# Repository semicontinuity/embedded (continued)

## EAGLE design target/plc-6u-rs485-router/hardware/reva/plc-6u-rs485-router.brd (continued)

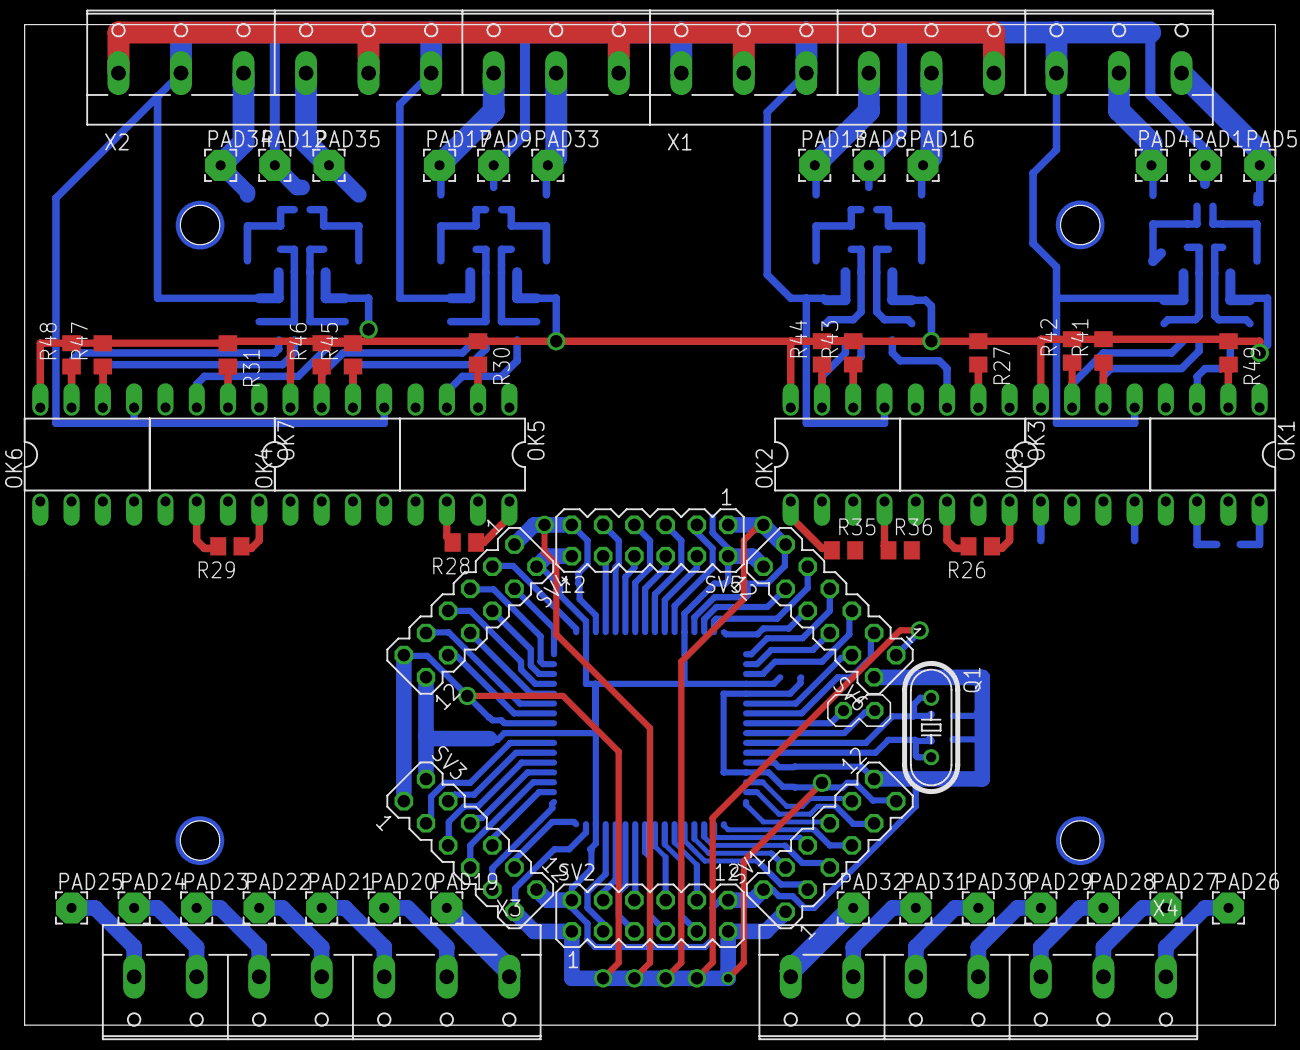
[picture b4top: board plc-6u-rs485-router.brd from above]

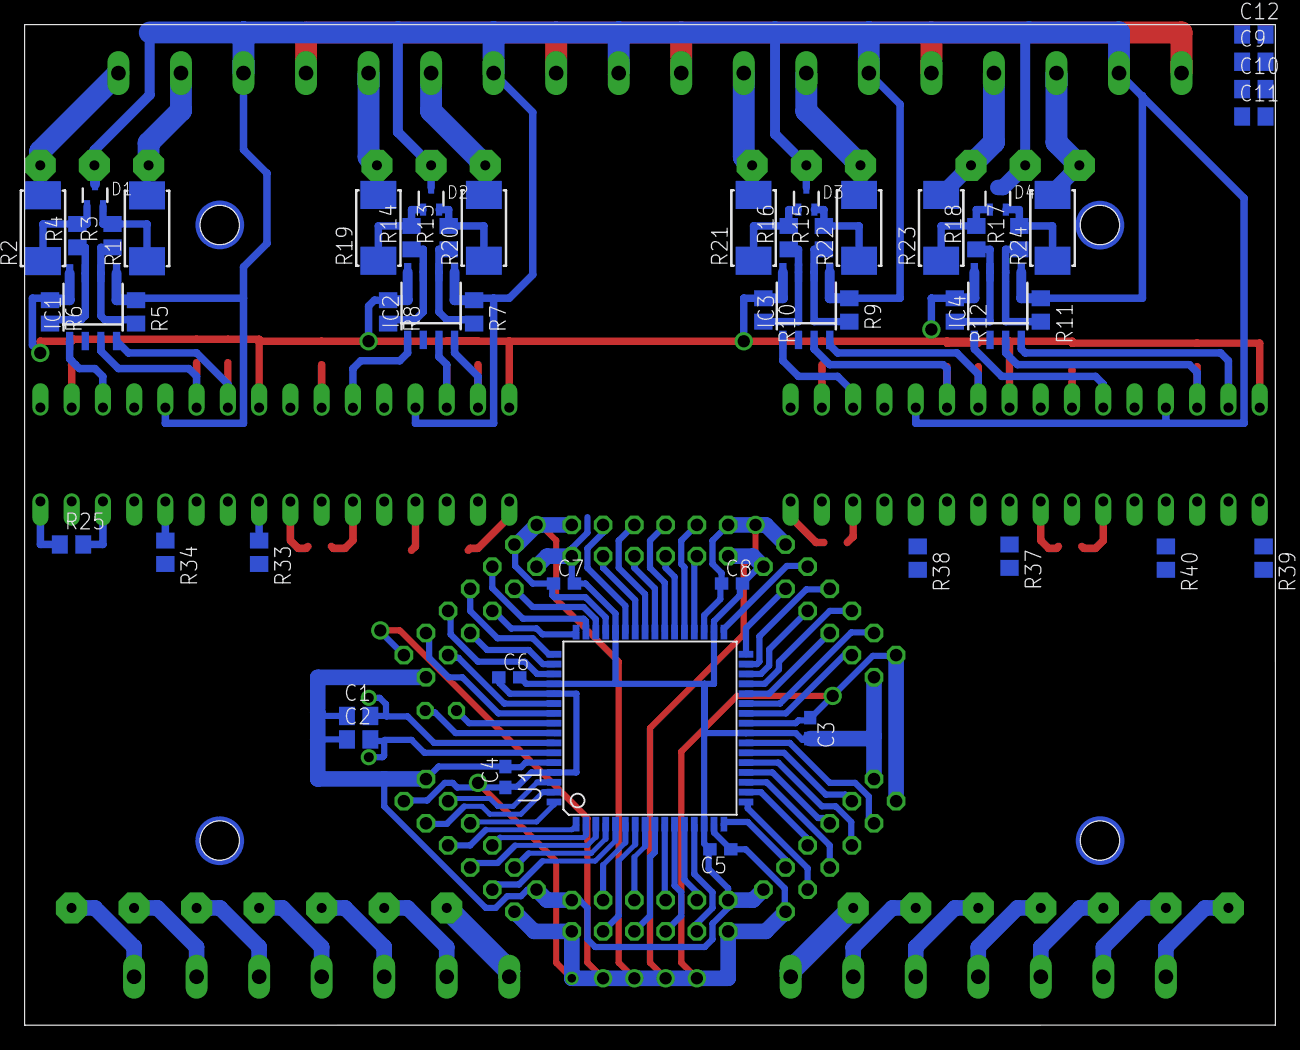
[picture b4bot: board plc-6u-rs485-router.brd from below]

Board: 2 copper layers, 101.6 x 81.3 mm, 115 parts (52 on the bottom side), 123 nets.

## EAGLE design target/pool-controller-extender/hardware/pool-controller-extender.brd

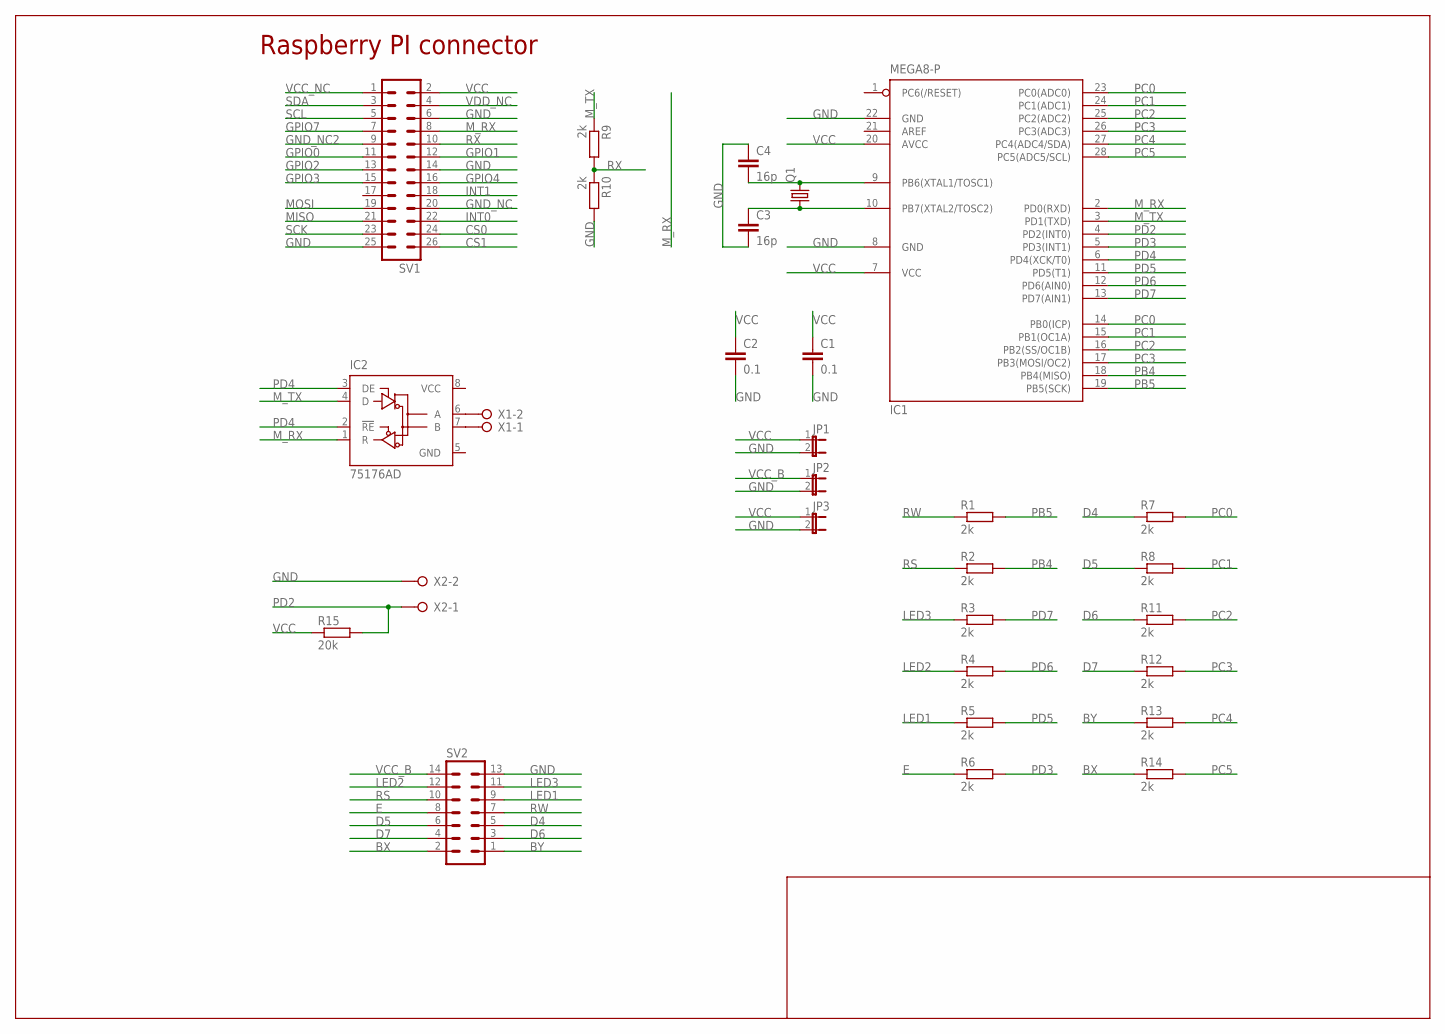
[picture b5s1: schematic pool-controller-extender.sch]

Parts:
C1, C2: 0.1; C0805
C3, C4: 16p; C0805
IC1: MEGA8-P; DIL28-3
IC2: 75176AD; D_R-PDSO-G8
JP1, JP2, JP3: JP1E; JP1
Q1: CRYSTALHC49S; HC49/S
R1, R2, R3, R4, R5, R6, R7, R8, R9, R10, R11, R12, R13, R14: 2k; R0805
R15: 20k; R0805
SV1: MA13-2
SV2: MA07-2W
X1, X2: W237-02P; W237-132

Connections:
BX: R14.1, SV2.2
BY: R13.1, SV2.1
CS0: SV1.24
CS1: SV1.26
D4: R7.1, SV2.5
D5: R8.1, SV2.6
D6: R11.1, SV2.3
D7: R12.1, SV2.4
E: R6.1, SV2.8
GND: C1.2, C2.2, C3.2, C4.1, IC1.8 (GND), IC1.22 (GND), IC2.5 (GND), JP1.2, JP2.2, JP3.2, R10.2, SV1.6, SV1.14, SV1.25, SV2.13, X2.2
GND_NC: SV1.20
GND_NC2: SV1.9
GPIO0: SV1.11
GPIO1: SV1.12
GPIO2: SV1.13
GPIO3: SV1.15
GPIO4: SV1.16
GPIO7: SV1.7
INT0: SV1.22
INT1: SV1.18
LED1: R5.1, SV2.9
LED2: R4.1, SV2.12
LED3: R3.1, SV2.11
MISO: SV1.21
MOSI: SV1.19
M_RX: IC1.2 (PD0(RXD)), IC2.1 (R), SV1.8
M_TX: IC1.3 (PD1(TXD)), IC2.4 (D), R9.1
unnamed: IC2.6 (A), X1.2
unnamed: IC2.7 (B), X1.1
unnamed: C3.1, IC1.10 (PB7(XTAL2/TOSC2)), Q1.1
unnamed: C4.2, IC1.9 (PB6(XTAL1/TOSC1)), Q1.2
PB4: IC1.18 (PB4(MISO)), R2.2
PB5: IC1.19 (PB5(SCK)), R1.2
PC0: IC1.14 (PB0(ICP)), IC1.23 (PC0(ADC0)), R7.2
PC1: IC1.15 (PB1(OC1A)), IC1.24 (PC1(ADC1)), R8.2
PC2: IC1.16 (PB2(SS/OC1B)), IC1.25 (PC2(ADC2)), R11.2
PC3: IC1.17 (PB3(MOSI/OC2)), IC1.26 (PC3(ADC3)), R12.2
PC4: IC1.27 (PC4(ADC4/SDA)), R13.2
PC5: IC1.28 (PC5(ADC5/SCL)), R14.2
PD2: IC1.4 (PD2(INT0)), R15.2, X2.1
PD3: IC1.5 (PD3(INT1)), R6.2
PD4: IC1.6 (PD4(XCK/T0)), IC2.2 (!RE), IC2.3 (DE)
PD5: IC1.11 (PD5(T1)), R5.2
PD6: IC1.12 (PD6(AIN0)), R4.2
PD7: IC1.13 (PD7(AIN1)), R3.2
RS: R2.1, SV2.10
RW: R1.1, SV2.7
RX: R9.2, R10.1, SV1.10
SCK: SV1.23
SCL: SV1.5
SDA: SV1.3
VCC: C1.1, C2.1, IC1.7 (VCC), IC1.20 (AVCC), IC2.8 (VCC), JP1.1, JP3.1, R15.1, SV1.2
VCC_B: JP2.1, SV2.14
VCC_NC: SV1.1
VDD_NC: SV1.4

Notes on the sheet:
Raspberry PI connector

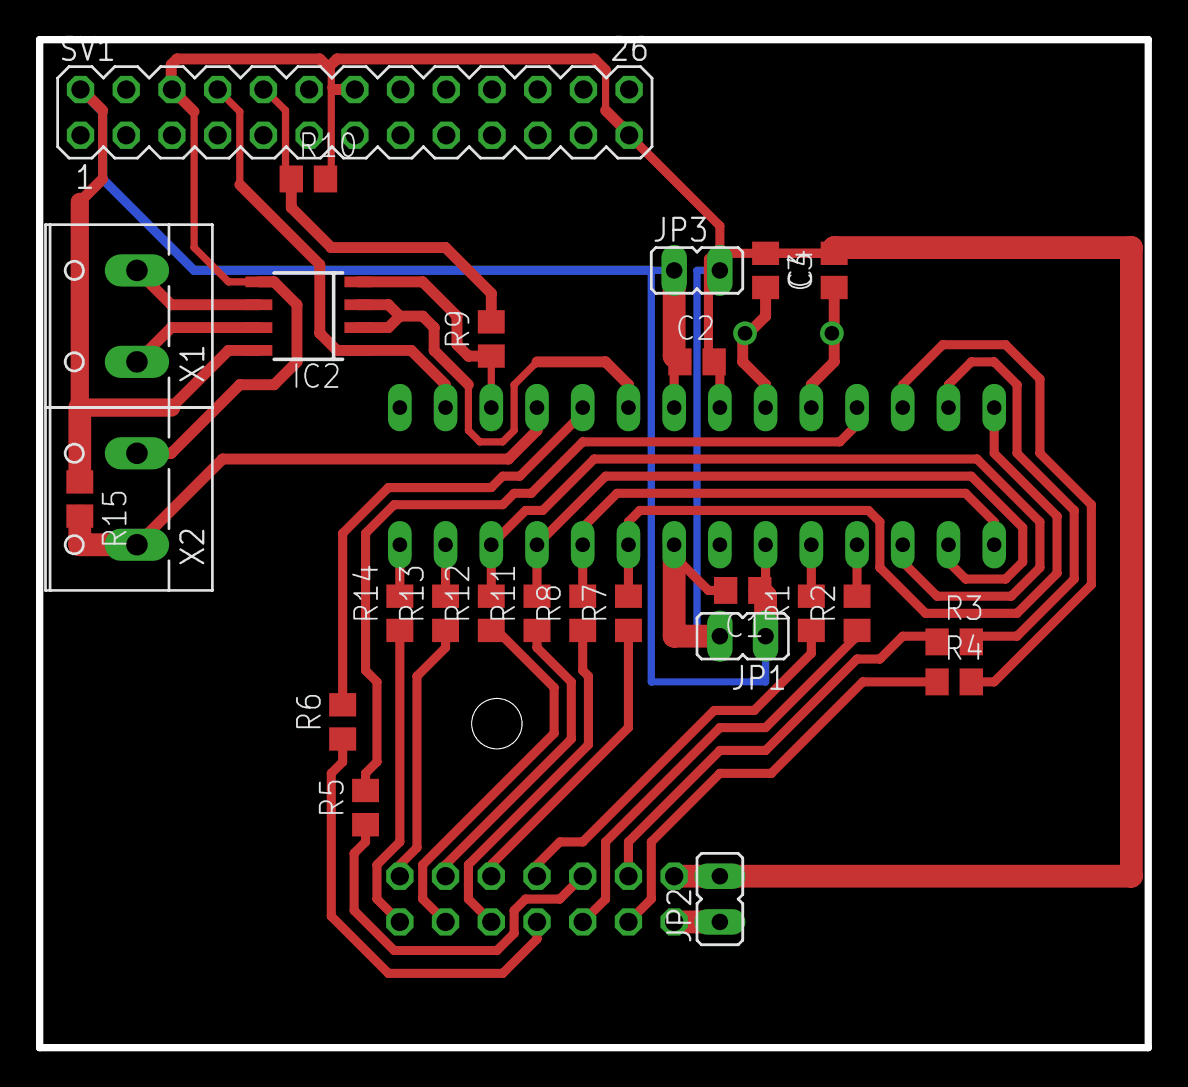
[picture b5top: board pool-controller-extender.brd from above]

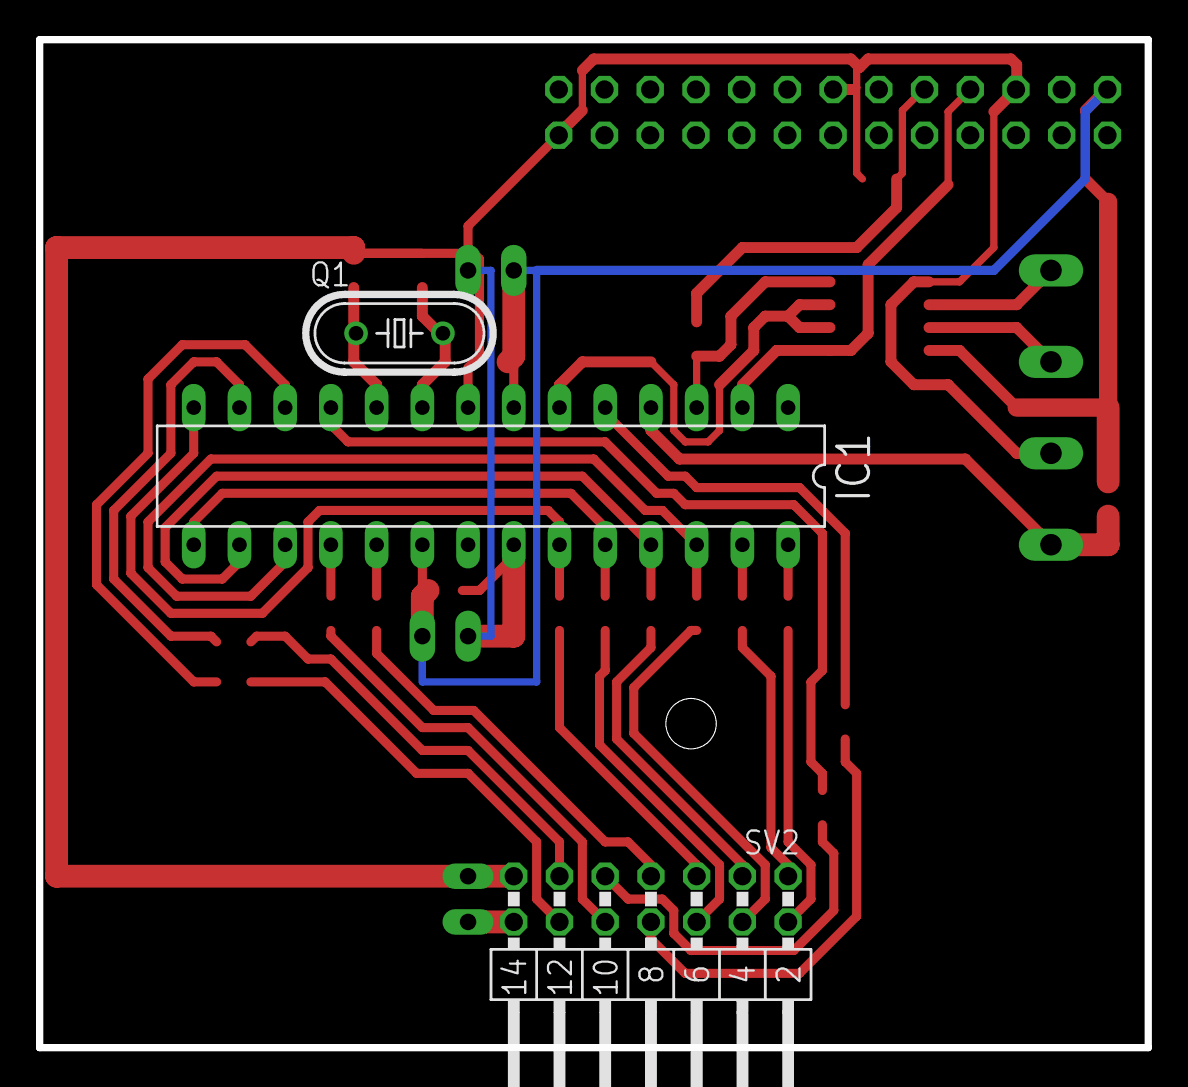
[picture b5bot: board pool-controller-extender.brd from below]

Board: 2 copper layers, 61.6 x 56.0 mm, 29 parts (3 on the bottom side), 36 nets.

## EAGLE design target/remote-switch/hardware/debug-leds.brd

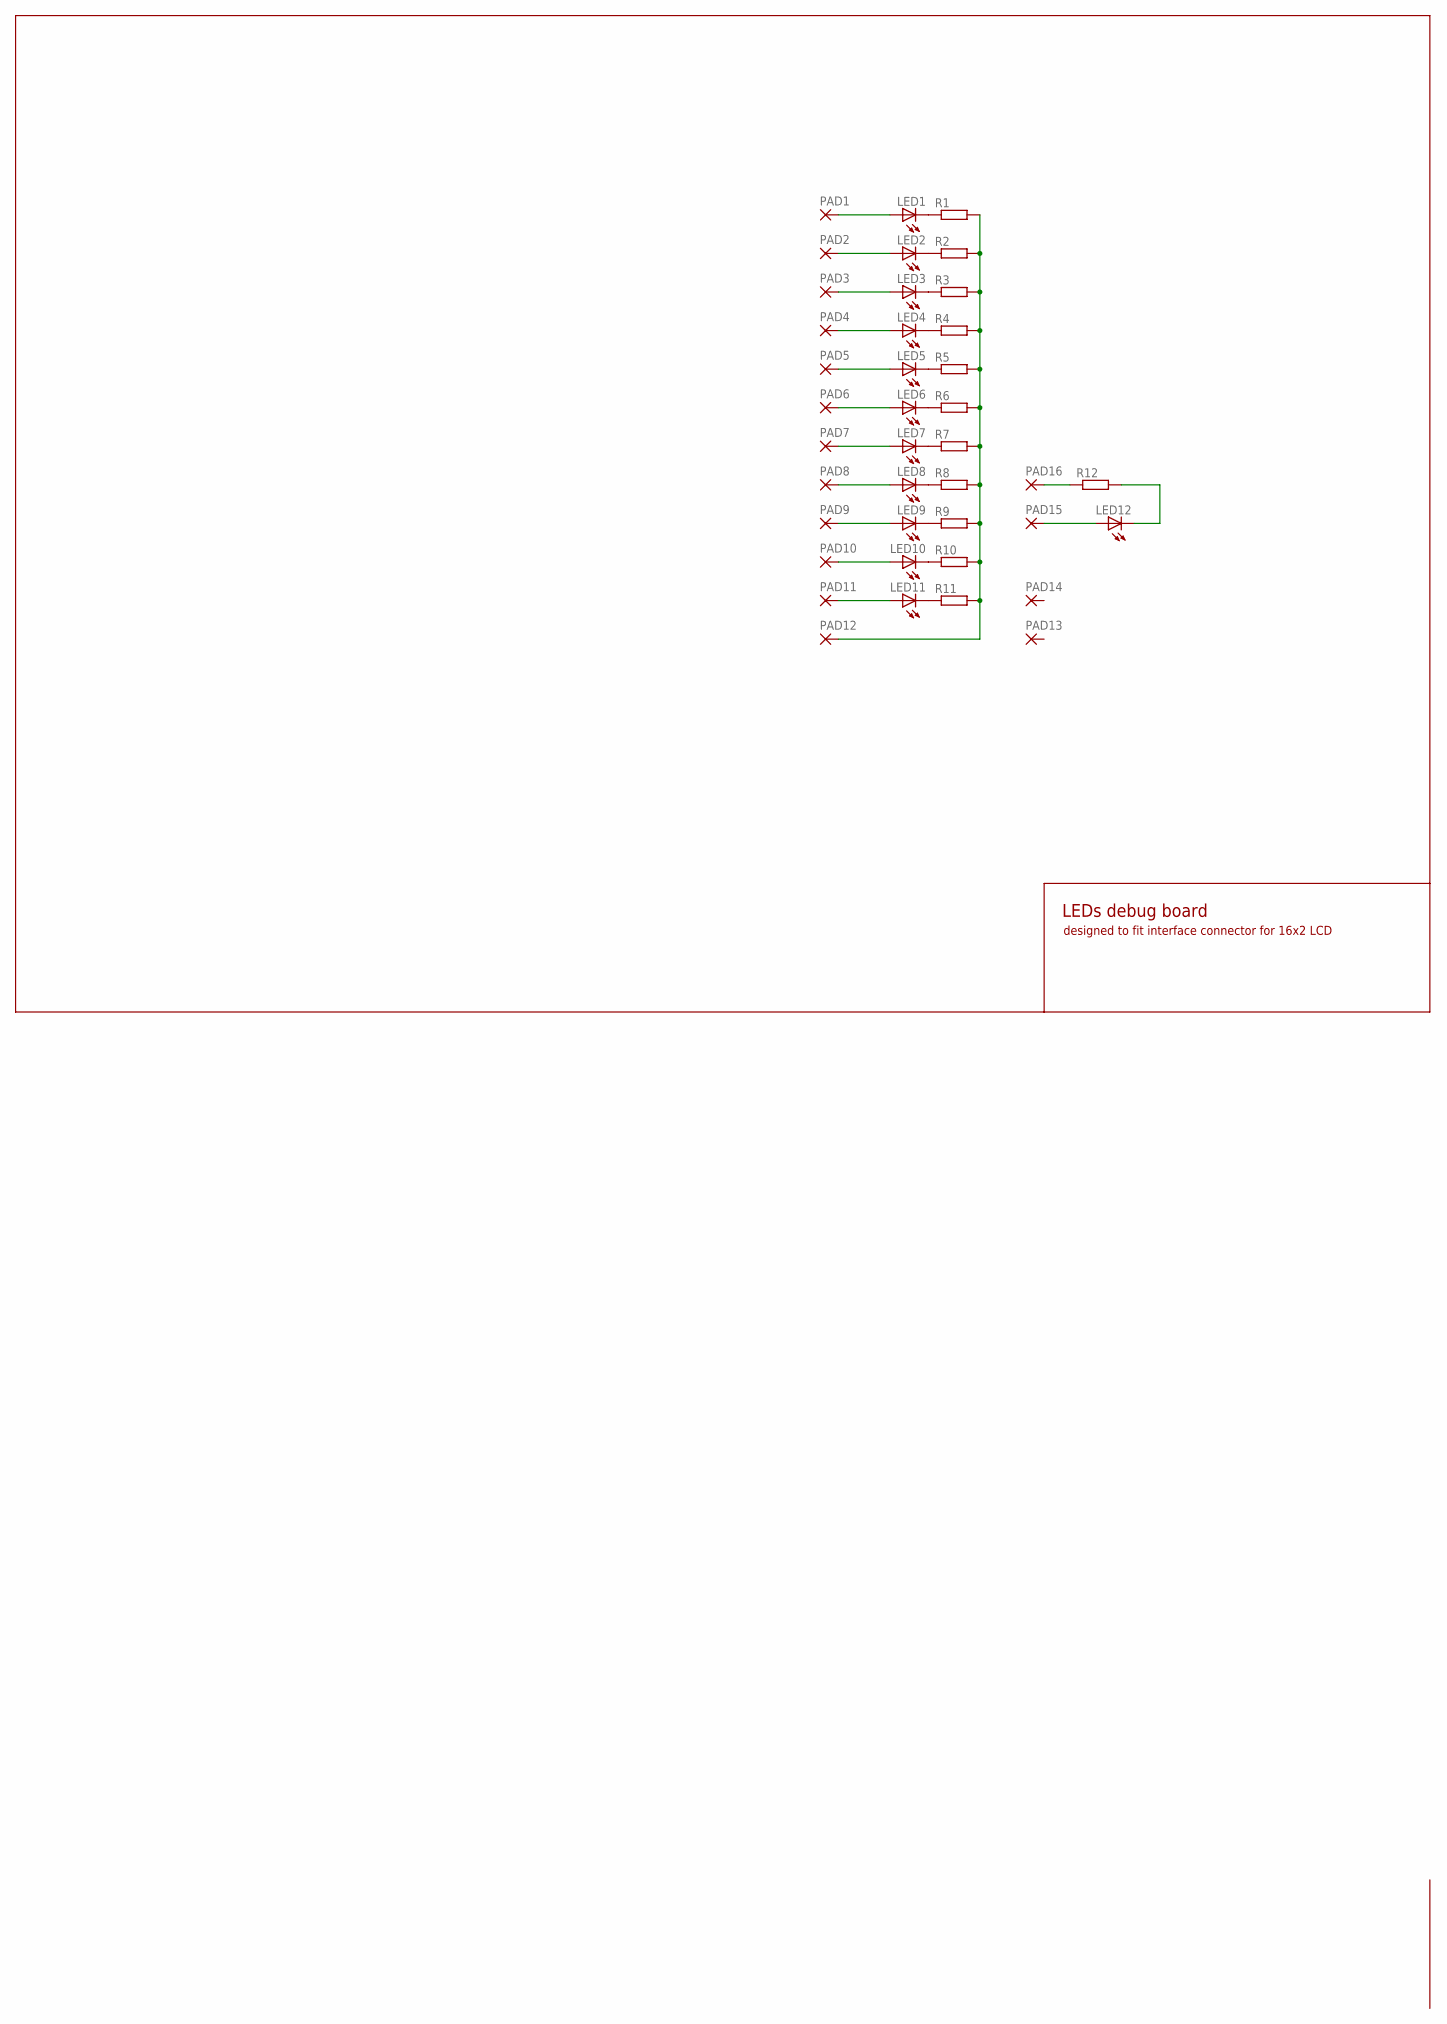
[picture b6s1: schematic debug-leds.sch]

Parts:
LED1, LED2, LED3, LED4, LED5, LED6, LED7, LED8, LED9, LED10, LED11, LED12: LEDSML0805; SML0805
PAD1, PAD2, PAD3, PAD4, PAD5, PAD6, PAD7, PAD8, PAD9, PAD10, PAD11, PAD12, PAD13, PAD14, PAD15, PAD16: 1,6/0,8
R1, R2, R3, R4, R5, R6, R7, R8, R9, R10, R11, R12: R-EU_M0805; M0805

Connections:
D6: LED2.A, PAD2.1
D7: LED1.A, PAD1.1
GND: PAD12.1, R1.2, R2.2, R3.2, R4.2, R5.2, R6.2, R7.2, R8.2, R9.2, R10.2, R11.2
unnamed: LED9.A, PAD9.1
unnamed: LED10.A, PAD10.1
unnamed: LED3.A, PAD3.1
unnamed: LED4.A, PAD4.1
unnamed: LED5.A, PAD5.1
unnamed: LED6.A, PAD6.1
unnamed: LED7.A, PAD7.1
unnamed: LED8.A, PAD8.1
unnamed: LED1.C, R1.1
unnamed: LED2.C, R2.1
unnamed: LED3.C, R3.1
unnamed: LED4.C, R4.1
unnamed: LED5.C, R5.1
unnamed: LED6.C, R6.1
unnamed: LED7.C, R7.1
unnamed: LED8.C, R8.1
unnamed: LED11.A, PAD11.1
unnamed: LED9.C, R9.1
unnamed: LED10.C, R10.1
unnamed: LED11.C, R11.1
unnamed: LED12.A, PAD15.1
unnamed: LED12.C, R12.2
unnamed: PAD16.1, R12.1

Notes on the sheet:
LEDs debug board
designed to fit interface connector for 16x2 LCD

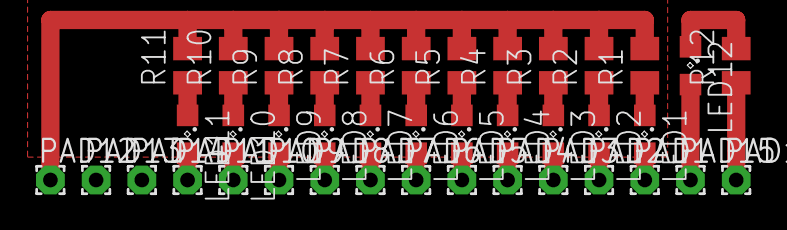
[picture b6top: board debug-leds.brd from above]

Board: 2 copper layers, 40 parts (0 on the bottom side), 26 nets.
